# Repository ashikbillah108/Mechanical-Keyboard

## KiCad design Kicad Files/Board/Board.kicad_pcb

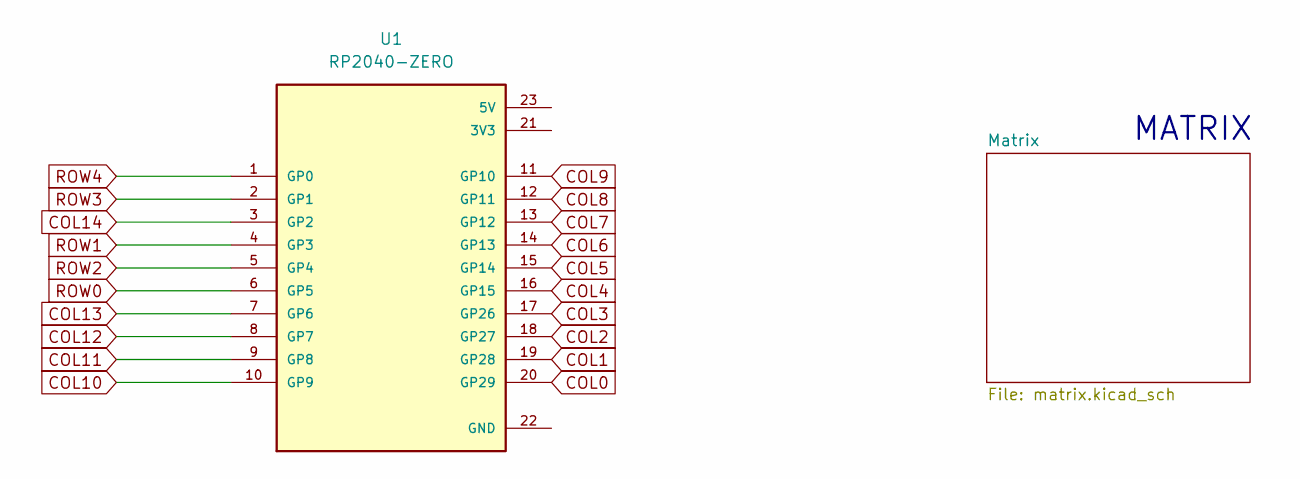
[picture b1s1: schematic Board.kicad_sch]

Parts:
U1: RP2040-ZERO; MODULE_RP2040-ZERO; LCSC Part # C5350143

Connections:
COL0: U1.20 (GP29); also elsewhere on the board
COL1: U1.19 (GP28); also elsewhere on the board
COL2: U1.18 (GP27); also elsewhere on the board
COL3: U1.17 (GP26); also elsewhere on the board
COL4: U1.16 (GP15); also elsewhere on the board
COL5: U1.15 (GP14); also elsewhere on the board
COL6: U1.14 (GP13); also elsewhere on the board
COL7: U1.13 (GP12); also elsewhere on the board
COL8: U1.12 (GP11); also elsewhere on the board
COL9: U1.11 (GP10); also elsewhere on the board
COL10: U1.10 (GP9); also elsewhere on the board
COL11: U1.9 (GP8); also elsewhere on the board
COL12: U1.8 (GP7); also elsewhere on the board
COL13: U1.7 (GP6); also elsewhere on the board
COL14: U1.3 (GP2); also elsewhere on the board
ROW0: U1.6 (GP5); also elsewhere on the board
ROW1: U1.4 (GP3); also elsewhere on the board
ROW2: U1.5 (GP4); also elsewhere on the board
ROW3: U1.2 (GP1); also elsewhere on the board
ROW4: U1.1 (GP0); also elsewhere on the board

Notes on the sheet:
MATRIX

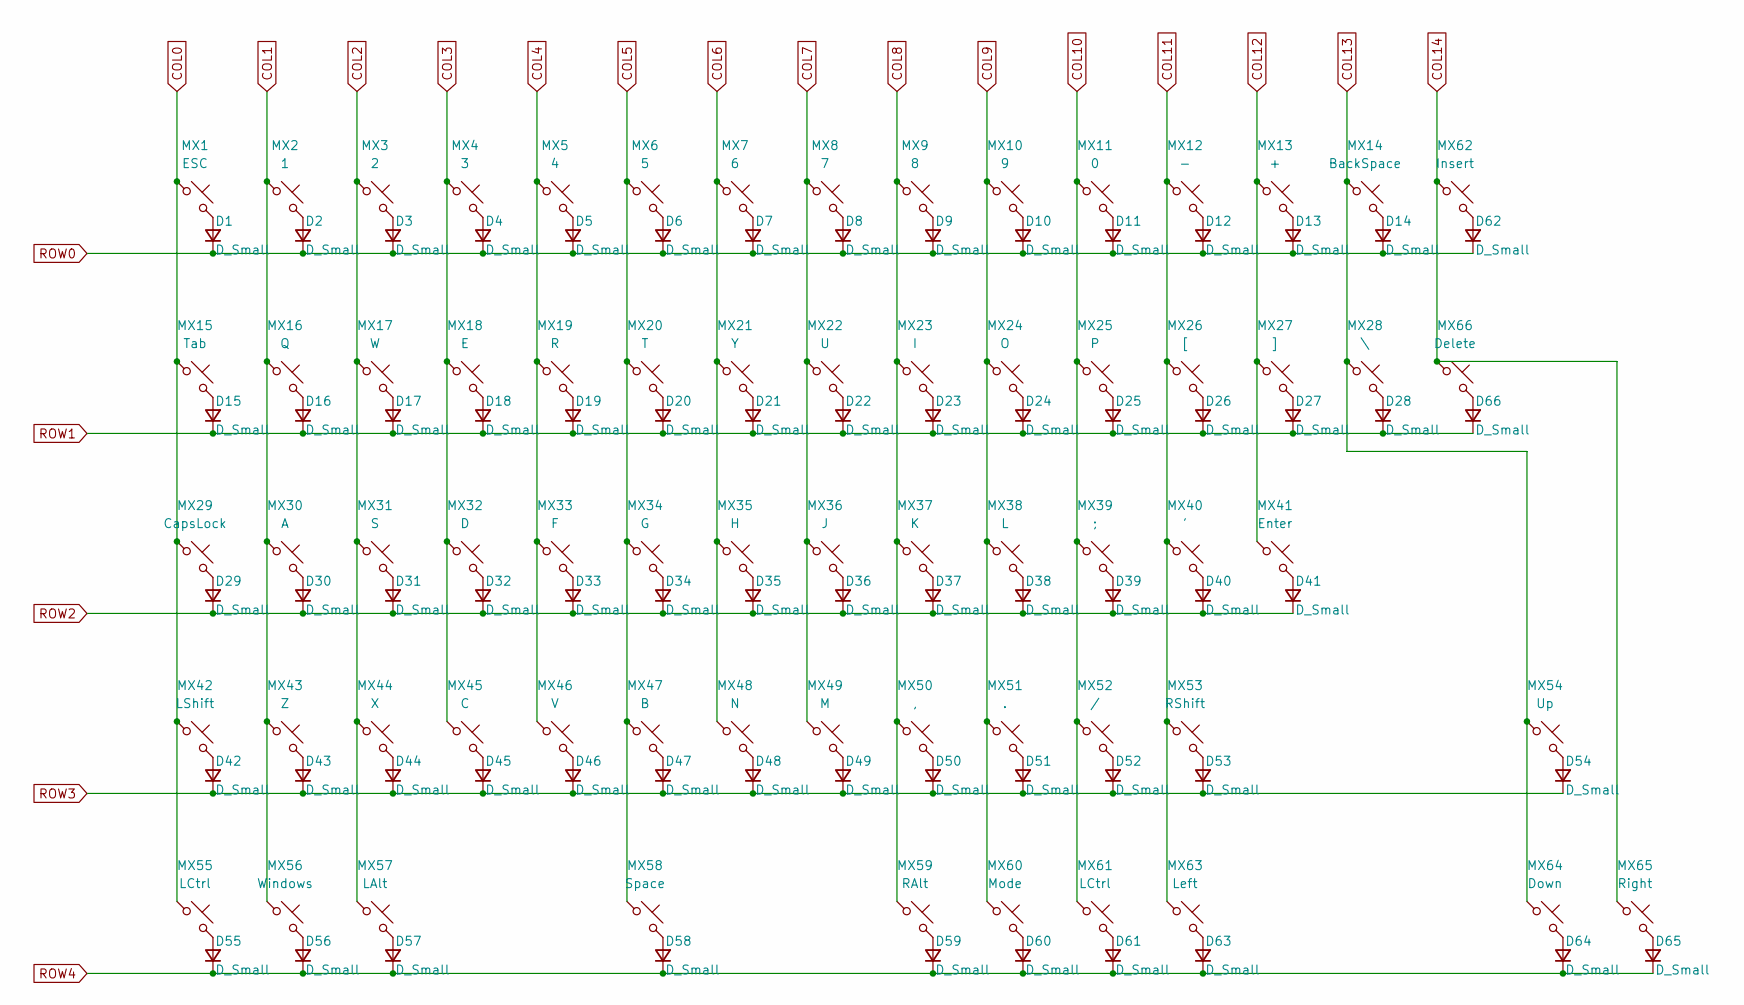
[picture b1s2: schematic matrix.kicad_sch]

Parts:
D1, D2, D3, D4, D5, D6, D7, D8, D9, D10, D11, D12, D13, D14, D15, D16, D17, D18, D19, D20, D21, D22, D23, D24, D25, D26, D27, D28, D29, D30, D31, D32, D33, D34, D35, D36, D37, D38, D39, D40, D41, D42, D43, D44, D45, D46, D47, D48, D49, D50, D51, D52, D53, D54, D55, D56, D57, D58, D59, D60, D61, D62, D63, D64, D65, D66: D_Small; D_0402_1005Metric
MX1: ESC; SW_Cherry_MX_1.00u_PCB
MX2: 1; SW_Cherry_MX_1.00u_PCB
MX3: 2; SW_Cherry_MX_1.00u_PCB
MX4: 3; SW_Cherry_MX_1.00u_PCB
MX5: 4; SW_Cherry_MX_1.00u_PCB
MX6: 5; SW_Cherry_MX_1.00u_PCB
MX7: 6; SW_Cherry_MX_1.00u_PCB
MX8: 7; SW_Cherry_MX_1.00u_PCB
MX9: 8; SW_Cherry_MX_1.00u_PCB
MX10: 9; SW_Cherry_MX_1.00u_PCB
MX11: 0; SW_Cherry_MX_1.00u_PCB
MX12: -; SW_Cherry_MX_1.00u_PCB
MX13: +; SW_Cherry_MX_1.00u_PCB
MX14: BackSpace; SW_Cherry_MX_1.00u_PCB
MX15: Tab; SW_Cherry_MX_1.00u_PCB
MX16: Q; SW_Cherry_MX_1.00u_PCB
MX17: W; SW_Cherry_MX_1.00u_PCB
MX18: E; SW_Cherry_MX_1.00u_PCB
MX19: R; SW_Cherry_MX_1.00u_PCB
MX20: T; SW_Cherry_MX_1.00u_PCB
MX21: Y; SW_Cherry_MX_1.00u_PCB
MX22: U; SW_Cherry_MX_1.00u_PCB
MX23: I; SW_Cherry_MX_1.00u_PCB
MX24: O; SW_Cherry_MX_1.00u_PCB
MX25: P; SW_Cherry_MX_1.00u_PCB
MX26: [; SW_Cherry_MX_1.00u_PCB
MX27: ]; SW_Cherry_MX_1.00u_PCB
MX28: \; SW_Cherry_MX_1.00u_PCB
MX29: CapsLock; SW_Cherry_MX_1.00u_PCB
MX30: A; SW_Cherry_MX_1.00u_PCB
MX31: S; SW_Cherry_MX_1.00u_PCB
MX32: D; SW_Cherry_MX_1.00u_PCB
MX33: F; SW_Cherry_MX_1.00u_PCB
MX34: G; SW_Cherry_MX_1.00u_PCB
MX35: H; SW_Cherry_MX_1.00u_PCB
MX36: J; SW_Cherry_MX_1.00u_PCB
MX37: K; SW_Cherry_MX_1.00u_PCB
MX38: L; SW_Cherry_MX_1.00u_PCB
MX39: ;; SW_Cherry_MX_1.00u_PCB
MX40: '; SW_Cherry_MX_1.00u_PCB
MX41: Enter; SW_Cherry_MX_1.00u_PCB
MX42: LShift; SW_Cherry_MX_1.00u_PCB
MX43: Z; SW_Cherry_MX_1.00u_PCB
MX44: X; SW_Cherry_MX_1.00u_PCB
MX45: C; SW_Cherry_MX_1.00u_PCB
MX46: V; SW_Cherry_MX_1.00u_PCB
MX47: B; SW_Cherry_MX_1.00u_PCB
MX48: N; SW_Cherry_MX_1.00u_PCB
MX49: M; SW_Cherry_MX_1.00u_PCB
MX50: ,; SW_Cherry_MX_1.00u_PCB
MX51: .; SW_Cherry_MX_1.00u_PCB
MX52: /; SW_Cherry_MX_1.00u_PCB
MX53: RShift; SW_Cherry_MX_1.00u_PCB
MX54: Up; SW_Cherry_MX_1.00u_PCB
MX55, MX61: LCtrl; SW_Cherry_MX_1.00u_PCB
MX56: Windows; SW_Cherry_MX_1.00u_PCB
MX57: LAlt; SW_Cherry_MX_1.00u_PCB
MX58: Space; SW_Cherry_MX_1.00u_PCB
MX59: RAlt; SW_Cherry_MX_1.00u_PCB
MX60: Mode; SW_Cherry_MX_1.00u_PCB
MX62: Insert; SW_Cherry_MX_1.00u_PCB
MX63: Left; SW_Cherry_MX_1.00u_PCB
MX64: Down; SW_Cherry_MX_1.00u_PCB
MX65: Right; SW_Cherry_MX_1.00u_PCB
MX66: Delete; SW_Cherry_MX_1.00u_PCB

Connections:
COL0: MX1.1, MX15.1, MX29.1, MX42.1, MX55.1; also elsewhere on the board
COL1: MX2.1, MX16.1, MX30.1, MX43.1, MX56.1; also elsewhere on the board
COL2: MX3.1, MX17.1, MX31.1, MX44.1, MX57.1; also elsewhere on the board
COL3: MX4.1, MX18.1, MX32.1, MX45.1; also elsewhere on the board
COL4: MX5.1, MX19.1, MX33.1, MX46.1; also elsewhere on the board
COL5: MX6.1, MX20.1, MX34.1, MX47.1, MX58.1; also elsewhere on the board
COL6: MX7.1, MX21.1, MX35.1, MX48.1; also elsewhere on the board
COL7: MX8.1, MX22.1, MX36.1, MX49.1; also elsewhere on the board
COL8: MX9.1, MX23.1, MX37.1, MX50.1, MX59.1; also elsewhere on the board
COL9: MX10.1, MX24.1, MX38.1, MX51.1, MX60.1; also elsewhere on the board
COL10: MX11.1, MX25.1, MX39.1, MX52.1, MX61.1; also elsewhere on the board
COL11: MX12.1, MX26.1, MX40.1, MX53.1, MX63.1; also elsewhere on the board
COL12: MX13.1, MX27.1, MX41.1; also elsewhere on the board
COL13: MX14.1, MX28.1, MX54.1, MX64.1; also elsewhere on the board
COL14: MX62.1, MX65.1, MX66.1; also elsewhere on the board
unnamed: D1.2 (A), MX1.2
unnamed: D2.2 (A), MX2.2
unnamed: D3.2 (A), MX3.2
unnamed: D4.2 (A), MX4.2
unnamed: D5.2 (A), MX5.2
unnamed: D6.2 (A), MX6.2
unnamed: D7.2 (A), MX7.2
unnamed: D8.2 (A), MX8.2
unnamed: D9.2 (A), MX9.2
unnamed: D10.2 (A), MX10.2
unnamed: D11.2 (A), MX11.2
unnamed: D12.2 (A), MX12.2
unnamed: D13.2 (A), MX13.2
unnamed: D14.2 (A), MX14.2
unnamed: D15.2 (A), MX15.2
unnamed: D16.2 (A), MX16.2
unnamed: D17.2 (A), MX17.2
unnamed: D18.2 (A), MX18.2
unnamed: D19.2 (A), MX19.2
unnamed: D20.2 (A), MX20.2
unnamed: D21.2 (A), MX21.2
unnamed: D22.2 (A), MX22.2
unnamed: D23.2 (A), MX23.2
unnamed: D24.2 (A), MX24.2
unnamed: D25.2 (A), MX25.2
unnamed: D26.2 (A), MX26.2
unnamed: D27.2 (A), MX27.2
unnamed: D28.2 (A), MX28.2
unnamed: D29.2 (A), MX29.2
unnamed: D30.2 (A), MX30.2
unnamed: D31.2 (A), MX31.2
unnamed: D32.2 (A), MX32.2
unnamed: D33.2 (A), MX33.2
unnamed: D34.2 (A), MX34.2
unnamed: D35.2 (A), MX35.2
unnamed: D36.2 (A), MX36.2
unnamed: D37.2 (A), MX37.2
unnamed: D38.2 (A), MX38.2
unnamed: D39.2 (A), MX39.2
unnamed: D40.2 (A), MX40.2
unnamed: D41.2 (A), MX41.2
unnamed: D42.2 (A), MX42.2
unnamed: D43.2 (A), MX43.2
unnamed: D44.2 (A), MX44.2
unnamed: D45.2 (A), MX45.2
unnamed: D46.2 (A), MX46.2
unnamed: D47.2 (A), MX47.2
unnamed: D48.2 (A), MX48.2
unnamed: D49.2 (A), MX49.2
unnamed: D50.2 (A), MX50.2
unnamed: D51.2 (A), MX51.2
unnamed: D52.2 (A), MX52.2
unnamed: D53.2 (A), MX53.2
unnamed: D54.2 (A), MX54.2
unnamed: D55.2 (A), MX55.2
unnamed: D56.2 (A), MX56.2
unnamed: D57.2 (A), MX57.2
unnamed: D58.2 (A), MX58.2
unnamed: D59.2 (A), MX59.2
unnamed: D60.2 (A), MX60.2
unnamed: D61.2 (A), MX61.2
unnamed: D62.2 (A), MX62.2
unnamed: D63.2 (A), MX63.2
unnamed: D64.2 (A), MX64.2
unnamed: D65.2 (A), MX65.2
unnamed: D66.2 (A), MX66.2
ROW0: D1.1 (K), D2.1 (K), D3.1 (K), D4.1 (K), D5.1 (K), D6.1 (K), D7.1 (K), D8.1 (K), D9.1 (K), D10.1 (K), D11.1 (K), D12.1 (K), D13.1 (K), D14.1 (K), D62.1 (K); also elsewhere on the board
ROW1: D15.1 (K), D16.1 (K), D17.1 (K), D18.1 (K), D19.1 (K), D20.1 (K), D21.1 (K), D22.1 (K), D23.1 (K), D24.1 (K), D25.1 (K), D26.1 (K), D27.1 (K), D28.1 (K), D66.1 (K); also elsewhere on the board
ROW2: D29.1 (K), D30.1 (K), D31.1 (K), D32.1 (K), D33.1 (K), D34.1 (K), D35.1 (K), D36.1 (K), D37.1 (K), D38.1 (K), D39.1 (K), D40.1 (K), D41.1 (K); also elsewhere on the board
ROW3: D42.1 (K), D43.1 (K), D44.1 (K), D45.1 (K), D46.1 (K), D47.1 (K), D48.1 (K), D49.1 (K), D50.1 (K), D51.1 (K), D52.1 (K), D53.1 (K), D54.1 (K); also elsewhere on the board
ROW4: D55.1 (K), D56.1 (K), D57.1 (K), D58.1 (K), D59.1 (K), D60.1 (K), D61.1 (K), D63.1 (K), D64.1 (K), D65.1 (K); also elsewhere on the board

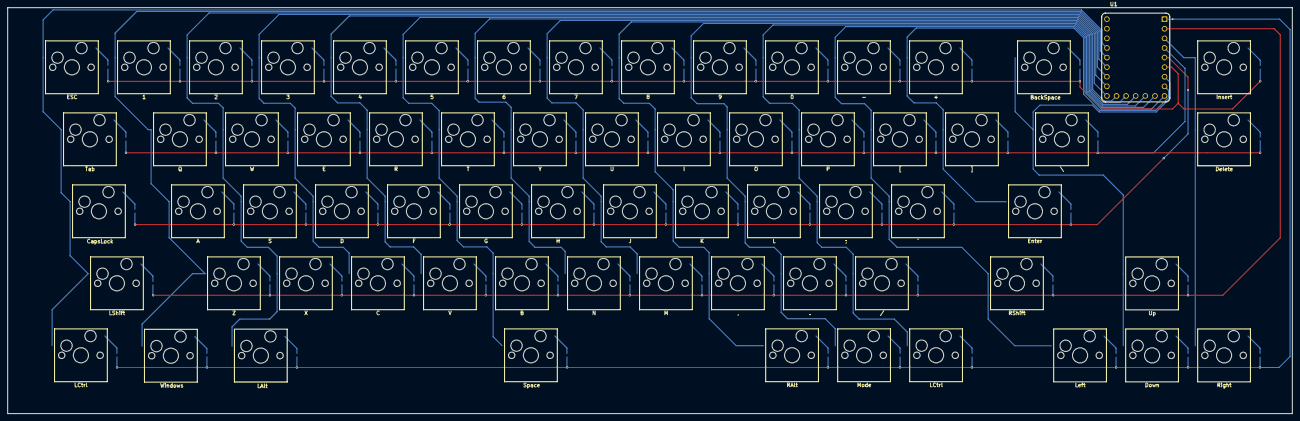
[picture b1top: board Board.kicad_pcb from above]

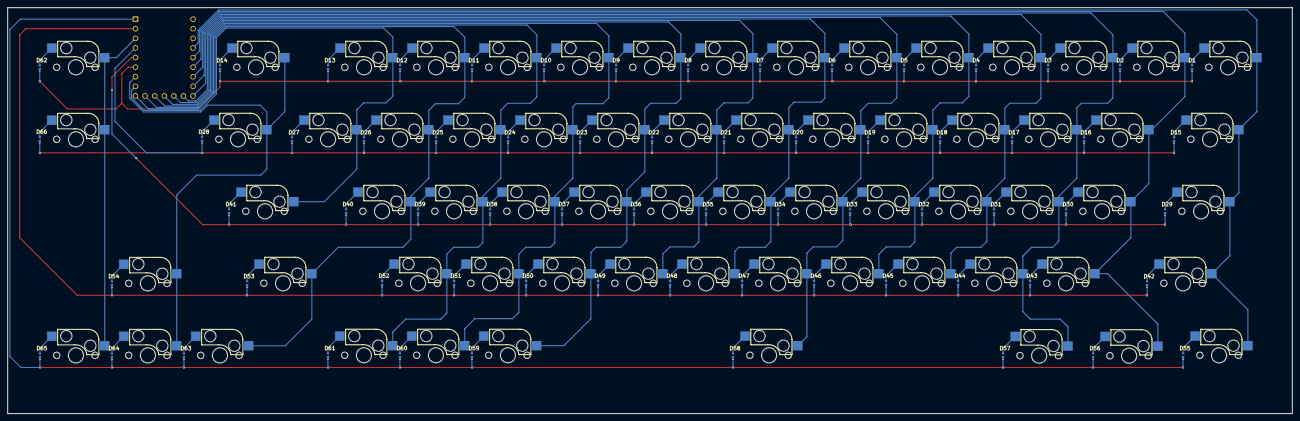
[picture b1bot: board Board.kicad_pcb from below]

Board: 2 copper layers, 339.9 x 107.4 mm, 133 parts (66 on the bottom side), 86 nets.

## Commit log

2024-12-04 Schematic Upload
2024-12-04 Modified Schematic
2024-12-04 Matrix Left
2024-12-05 Schematic - Matrix Reduction Needed
2024-12-11 PCB Space
2024-12-12 Matrix and Diode Done
2024-12-12 Switch Update
2024-12-12 Silkscreen updated
2025-01-26 Routing Completed
